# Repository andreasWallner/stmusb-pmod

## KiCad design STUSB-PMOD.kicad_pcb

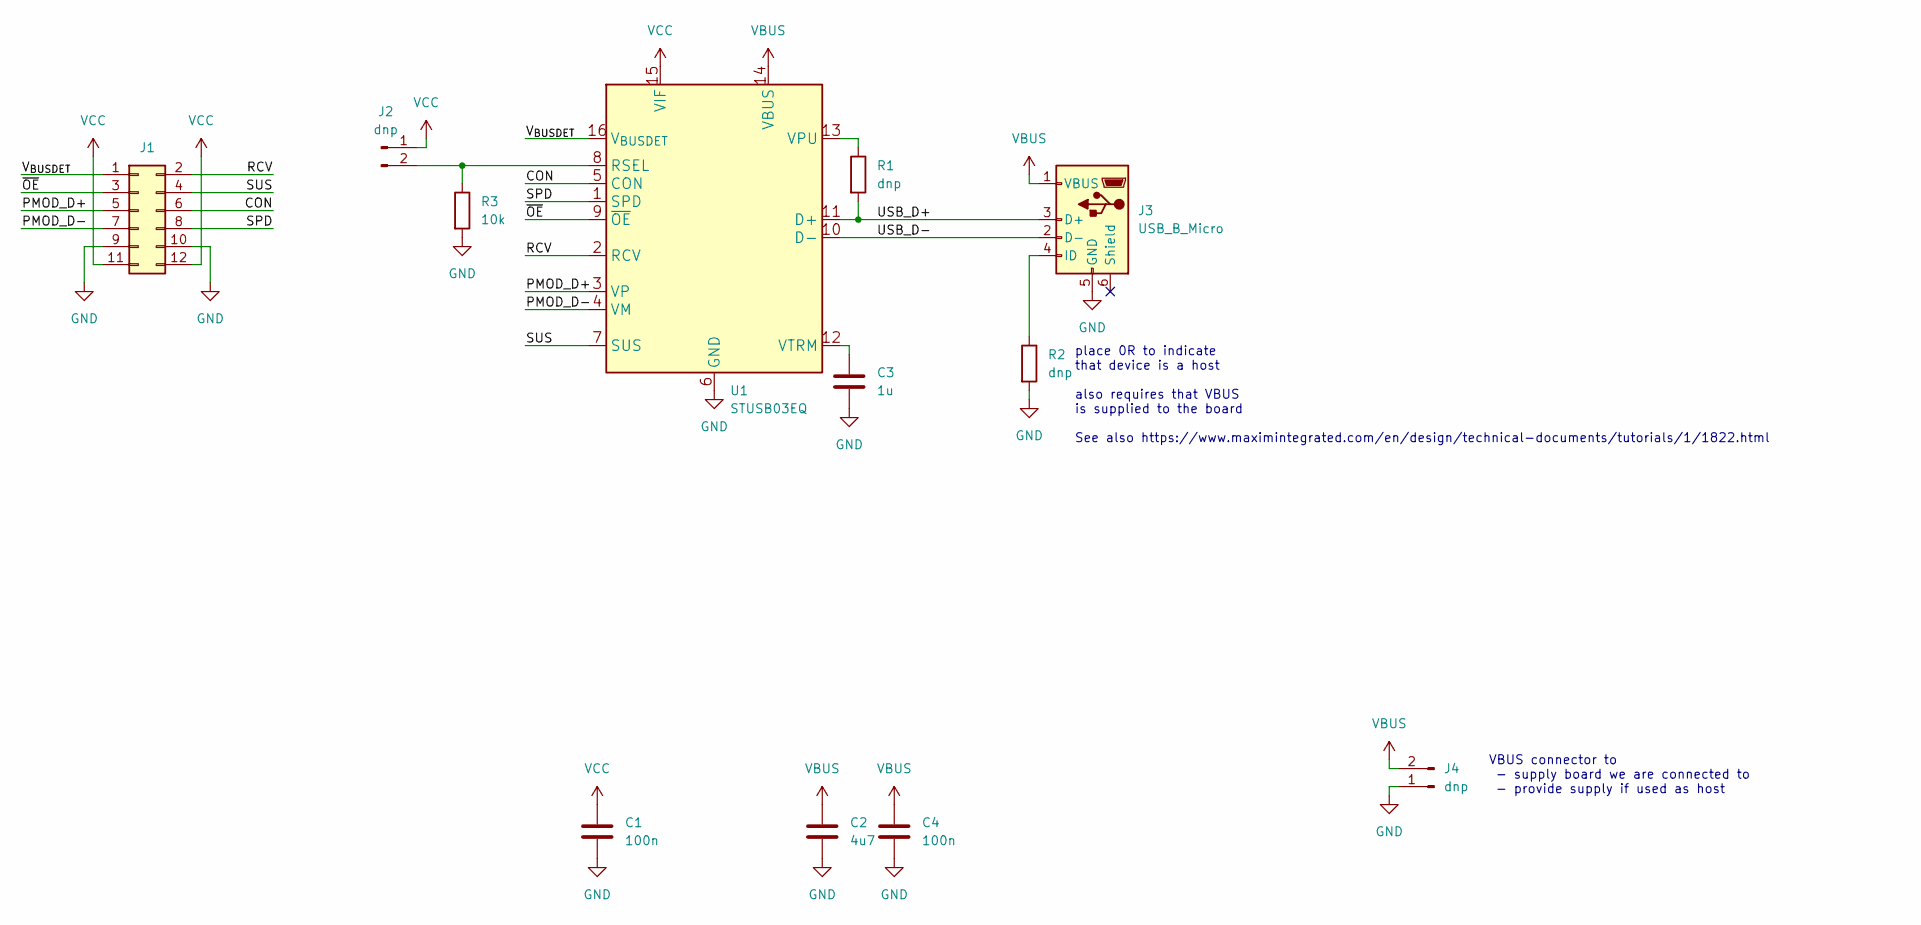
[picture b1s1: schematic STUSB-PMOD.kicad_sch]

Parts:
C1, C4: 100n; C_0603_1608Metric_Pad1.08x0.95mm_HandSolder; LCSC C14663
C2: 4u7; C_0805_2012Metric; LCSC C1779
C3: 1u; C_1206_3216Metric; LCSC C1848
J1: Conn_02x06_Odd_Even; PinHeaderMirrored_2x06_P2.54mm_Horizontal; LCSC C60565
J2, J4: dnp; PinHeader_1x02_P1.27mm_Vertical
J3: USB_B_Micro; MICRO5.9mmusb; LCSC C393940
R1, R2: dnp; R_0603_1608Metric_Pad0.98x0.95mm_HandSolder
R3: 10k; R_0603_1608Metric_Pad0.98x0.95mm_HandSolder
U1: STUSB03EQ; QFN-16-1EP_3x3mm_P0.5mm_EP1.7x1.7mm

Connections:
/CON: J1.6, U1.5 (CON)
/PMOD_D+: J1.5, U1.3 (VP)
/PMOD_D-: J1.7, U1.4 (VM)
/RCV: J1.2, U1.2 (RCV)
/SPD: J1.8, U1.1 (SPD)
/SUS: J1.4, U1.7 (SUS)
/USB_D+: J3.3 (D+), R1.2, U1.11 (D+)
/USB_D-: J3.2 (D-), U1.10 (D-)
/V_{BUSDET}: J1.1, U1.16 (V_{BUSDET})
/~OE: J1.3, U1.9 (~OE)
GND: C1.2, C2.2, C3.2, C4.2, J1.9, J1.10, J3.5 (GND), J4.1, R2.2, R3.2, U1.6 (GND)
unnamed: C3.1, U1.12 (VTRM)
unnamed: J2.2, R3.1, U1.8 (RSEL)
unnamed: J3.4 (ID), R2.1
unnamed: R1.1, U1.13 (VPU)
VBUS: C2.1, C4.1, J3.1 (VBUS), J4.2, U1.14 (VBUS)
VCC: C1.1, J1.11, J1.12, J2.1, U1.15 (VIF)

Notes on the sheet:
VBUS connector to - supply board we are connected to - provide supply if used as host
place 0R to indicate that device is a host also requires that VBUS is supplied to the board See also https://www.maximintegrated.com/en/design/technical-documents/tutorials/1/1822.html

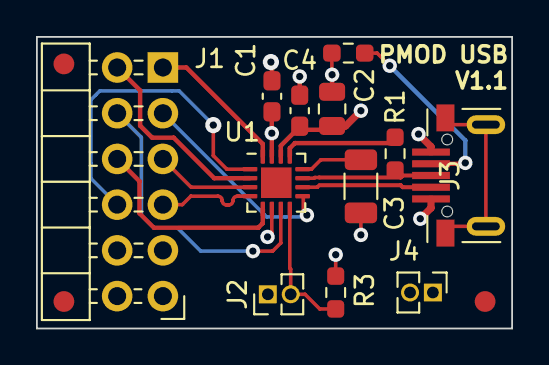
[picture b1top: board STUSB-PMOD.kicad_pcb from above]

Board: 4 copper layers, 26.4 x 16.2 mm, 12 parts (0 on the bottom side), 17 nets.

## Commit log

2022-11-12 First spin
2022-11-12 Move C3 to improve solderability
2022-11-12 fixup first
2023-04-07 Minor cleanup
